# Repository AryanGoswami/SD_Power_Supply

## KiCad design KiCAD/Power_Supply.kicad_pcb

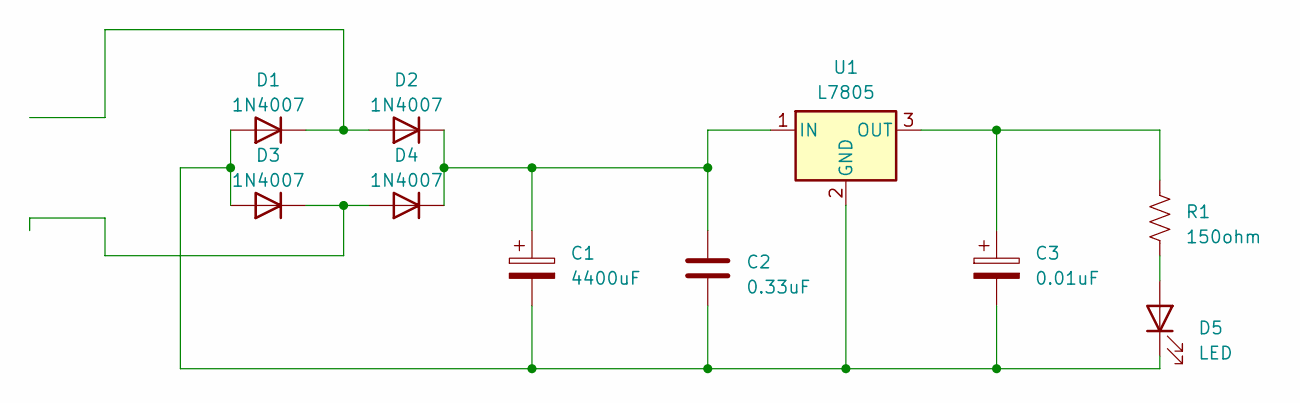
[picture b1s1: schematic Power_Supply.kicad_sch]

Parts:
C1: 4400uF; C_Radial_D16.0mm_H25.0mm_P7.50mm
C2: 0.33uF; CP_Radial_D8.0mm_P5.00mm
C3: 0.01uF; C_Disc_D7.5mm_W2.5mm_P5.00mm
D1, D2, D3, D4: 1N4007; D_DO-41_SOD81_P10.16mm_Horizontal
D5: LED; LED_D5.0mm
R1: 150ohm; R_Axial_DIN0207_L6.3mm_D2.5mm_P10.16mm_Horizontal
U1: L7805; TO-220-3_Vertical

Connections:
0: D3.1 (K), D4.2 (A)
unnamed: C1.2, C2.2, C3.2, D1.2 (A), D3.2 (A), D5.1 (K), U1.2 (GND)
unnamed: D1.1 (K), D2.2 (A)
unnamed: C1.1, C2.1, D2.1 (K), D4.1 (K), U1.1 (IN)
unnamed: D5.2 (A), R1.2
unnamed: C3.1, R1.1, U1.3 (OUT)

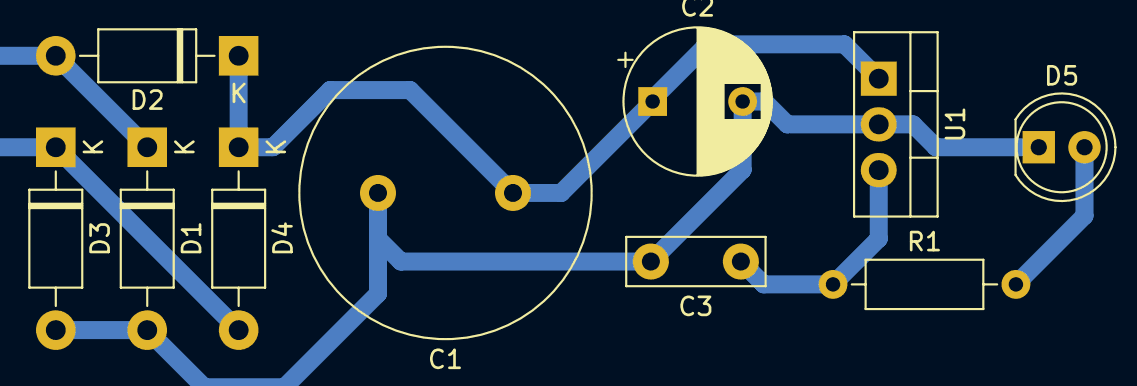
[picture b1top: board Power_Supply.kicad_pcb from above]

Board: 2 copper layers, 10 parts (0 on the bottom side), 6 nets.

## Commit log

2024-08-31 PCB Files
